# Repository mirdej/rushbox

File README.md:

# rushbox
controller for martin rush wash

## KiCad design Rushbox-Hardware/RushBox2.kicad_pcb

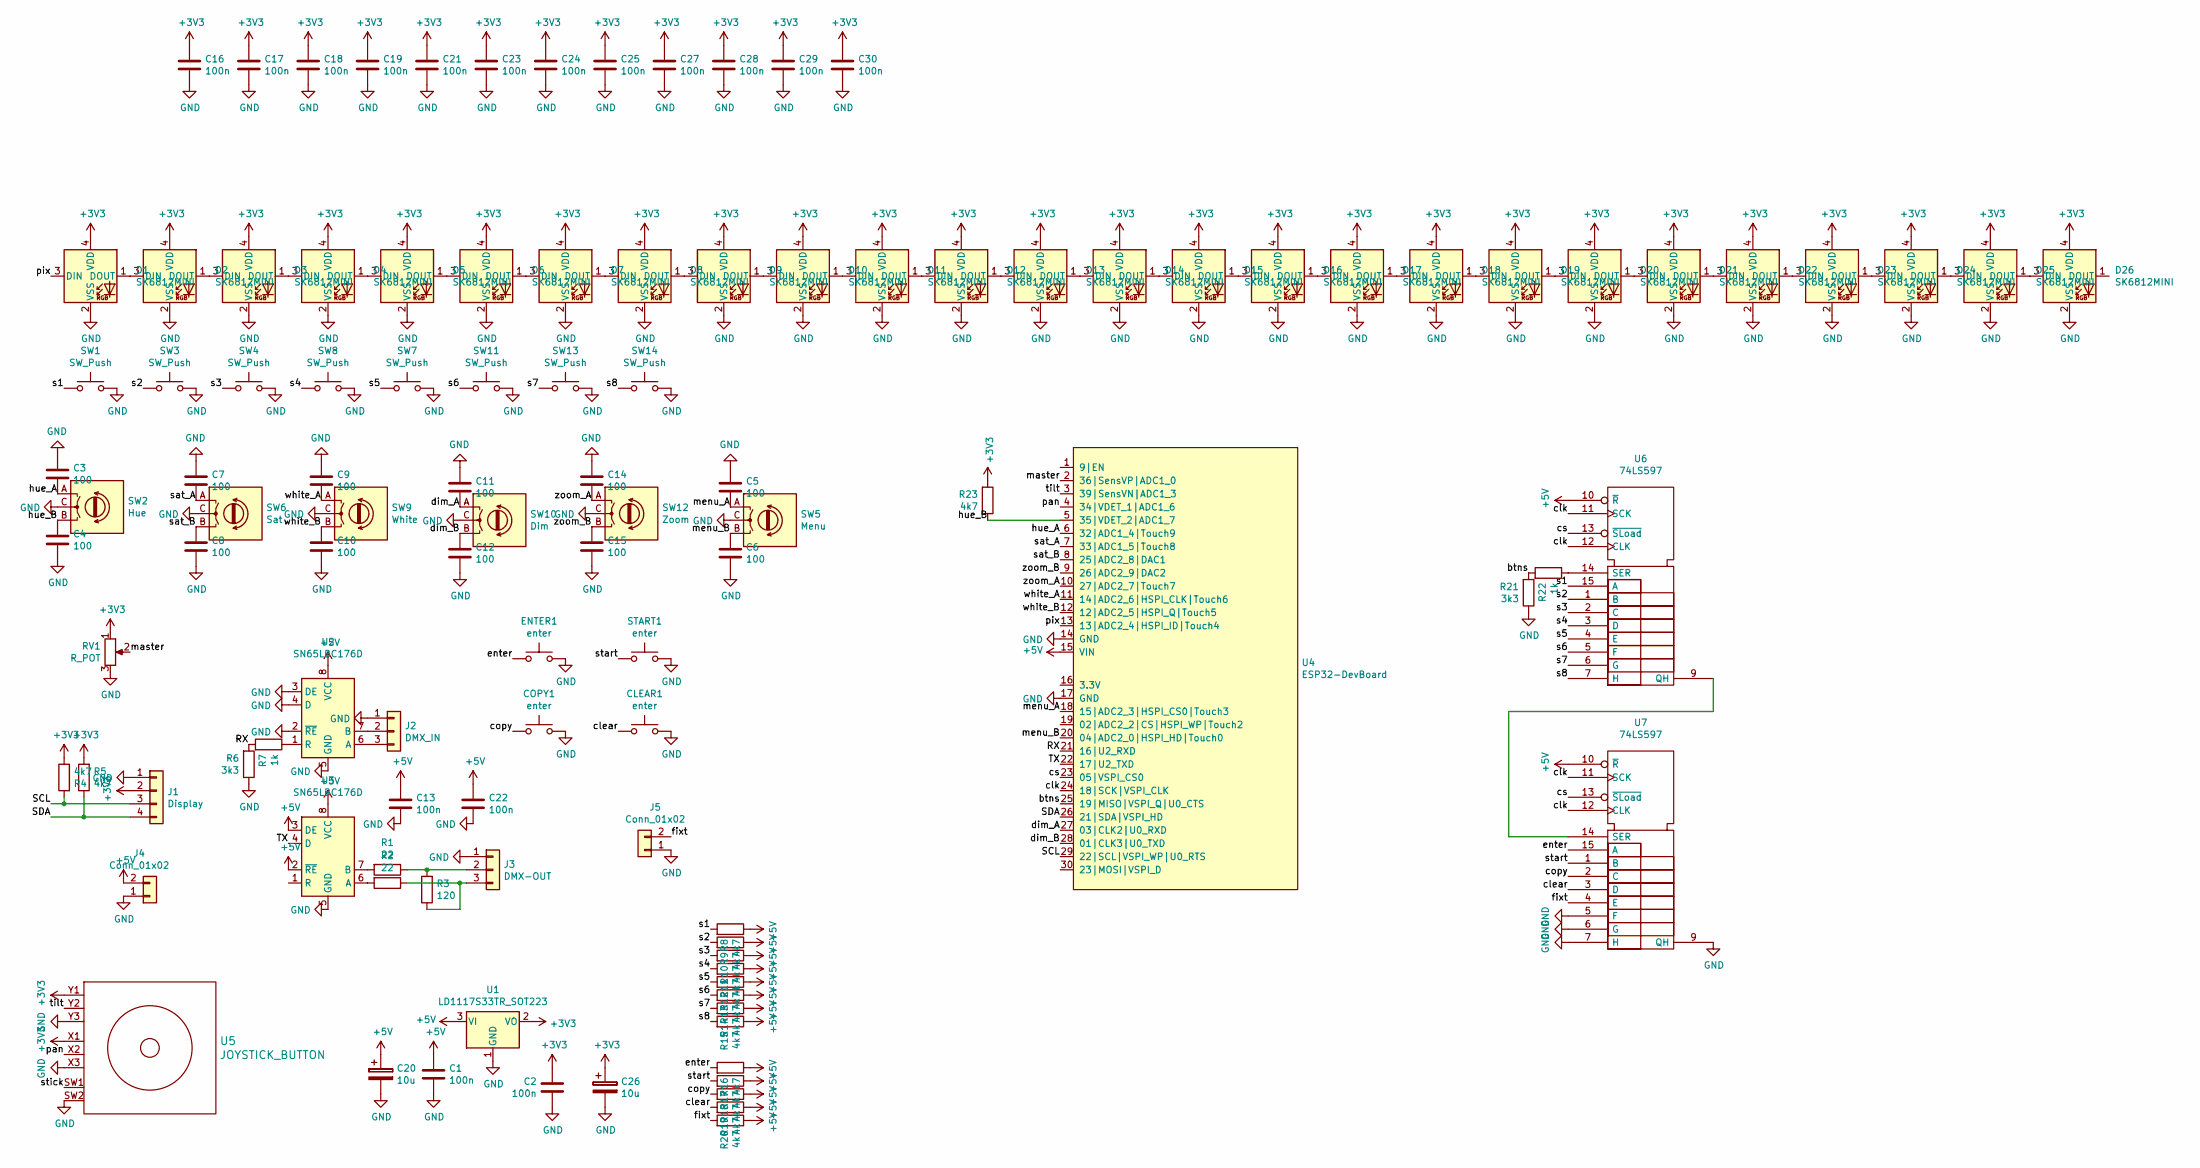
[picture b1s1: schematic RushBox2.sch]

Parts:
C1, C2, C13, C16, C17, C18, C19, C21, C22, C23, C24, C25, C27, C28, C29, C30: 100n; C_0603_1608Metric_Pad1.05x0.95mm_HandSolder
C3, C4, C5, C6, C7, C8, C9, C10, C11, C12, C14, C15: 100; C_0603_1608Metric_Pad1.05x0.95mm_HandSolder
C20, C26: 10u; CP_EIA-3528-21_Kemet-B_Pad1.50x2.35mm_HandSolder
CLEAR1: enter; SW_SPST_B3SL-1002P
COPY1: enter; SW_SPST_B3SL-1002P
D1, D2, D3, D4, D5, D6, D7, D8, D9, D10, D11, D12, D13, D14, D15, D16, D17, D18, D19, D20, D21, D22, D23, D24, D25, D26: SK6812MINI; LED_SK6812MINI_PLCC4_3.5x3.5mm_P1.75mm
ENTER1: enter; SW_SPST_B3SL-1002P
J1: Display; Bangood-OLED-128x32
J2: DMX_IN; Molex_KK-254_AE-6410-03A_1x03_P2.54mm_Vertical
J3: DMX-OUT; Molex_KK-254_AE-6410-03A_1x03_P2.54mm_Vertical
J4, J5: Conn_01x02; Molex_KK-254_AE-6410-02A_1x02_P2.54mm_Vertical
R1, R2: 22; R_0805_2012Metric_Pad1.15x1.40mm_HandSolder
R3: 120; R_0805_2012Metric_Pad1.15x1.40mm_HandSolder
R4, R5, R8, R9, R10, R11, R12, R13, R14, R15, R16, R17, R18, R19, R20, R23: 4k7; R_0805_2012Metric_Pad1.15x1.40mm_HandSolder
R6, R21: 3k3; R_0805_2012Metric_Pad1.15x1.40mm_HandSolder
R7, R22: 1k; R_0805_2012Metric_Pad1.15x1.40mm_HandSolder
RV1: R_POT; Potentiometer_Alps_RS6011xP_Slide
START1: enter; SW_SPST_B3SL-1002P
SW1, SW3, SW4, SW7, SW8, SW11, SW13, SW14: SW_Push; SW_SPST_B3SL-1002P
SW2: Hue; RotaryEncoder_Alps_EC12E_Vertical_H20mm
SW5: Menu; RotaryEncoder_Alps_EC12E_Vertical_H20mm
SW6: Sat; RotaryEncoder_Alps_EC12E_Vertical_H20mm
SW9: White; RotaryEncoder_Alps_EC12E_Vertical_H20mm
SW10: Dim; RotaryEncoder_Alps_EC12E_Vertical_H20mm
SW12: Zoom; RotaryEncoder_Alps_EC12E_Vertical_H20mm
U1: LD1117S33TR_SOT223; SOT-223-3_TabPin2
U2, U3: SN65LBC176D; SOIC-8_3.9x4.9mm_P1.27mm
U4: ESP32-DevBoard; ESP32_Devboard
U5: JOYSTICK_BUTTON; Joystick_Button
U6, U7: 74LS597; SOIC-16_3.9x9.9mm_P1.27mm

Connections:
+3V3: C2.2, C16.1, C17.1, C18.1, C19.1, C21.1, C23.1, C24.1, C25.1, C26.1, C27.1, C28.1, C29.1, C30.1, D1.4 (VDD), D2.4 (VDD), D3.4 (VDD), D4.4 (VDD), D5.4 (VDD), D6.4 (VDD), D7.4 (VDD), D8.4 (VDD), D9.4 (VDD), D10.4 (VDD), D11.4 (VDD), D12.4 (VDD), D13.4 (VDD), D14.4 (VDD), D15.4 (VDD), D16.4 (VDD), D17.4 (VDD), D18.4 (VDD), D19.4 (VDD), D20.4 (VDD), D21.4 (VDD), D22.4 (VDD), D23.4 (VDD), D24.4 (VDD), D25.4 (VDD), D26.4 (VDD), J1.2, R4.1, R5.2, R23.2, RV1.1, U1.2 (VO), U5.X1, U5.Y1
+5V: C1.1, C13.1, C20.1, C22.1, J4.2, R8.1, R9.1, R10.1, R11.1, R12.1, R13.1, R14.1, R15.1, R16.1, R17.1, R18.1, R19.1, R20.1, U1.3 (VI), U2.8 (VCC), U3.2 (~RE), U3.3 (DE), U3.8 (VCC), U4.15 (VIN), U6.10 (~R), U7.10 (~R)
/RX: R6.2, R7.2, U4.21 (16|U2_RXD)
/SCL: J1.3, R4.2, U4.29 (22|SCL|VSPI_WP|U0_RTS)
/SDA: J1.4, R5.1, U4.26 (21|SDA|VSPI_HD)
/TX: U3.4 (D), U4.22 (17|U2_TXD)
/btns: R21.2, R22.2, U4.25 (19|MISO|VSPI_Q|U0_CTS)
/clear: CLEAR1.1, R19.2, U7.3 (D)
/clk: U4.24 (18|SCK|VSPI_CLK), U6.11 (SCK), U6.12 (CLK), U7.11 (SCK), U7.12 (CLK)
/copy: COPY1.1, R18.2, U7.2 (C)
/cs: U4.23 (05|VSPI_CS0), U6.13 (~SLoad), U7.13 (~SLoad)
/dim_A: C11.2, SW10.A, U4.27 (03|CLK2|U0_RXD)
/dim_B: C12.1, SW10.B, U4.28 (01|CLK3|U0_TXD)
/enter: ENTER1.1, R16.2, U7.15 (A)
/fixt: J5.2, R20.2, U7.4 (E)
/hue_A: C3.2, SW2.A, U4.6 (32|ADC1_4|Touch9)
/hue_B: C4.1, R23.1, SW2.B, U4.5 (35|VDET_2|ADC1_7)
/master: RV1.2, U4.2 (36|SensVP|ADC1_0)
/menu_A: C5.2, SW5.A, U4.18 (15|ADC2_3|HSPI_CS0|Touch3)
/menu_B: C6.1, SW5.B, U4.20 (04|ADC2_0|HSPI_HD|Touch0)
/pan: U4.4 (34|VDET_1|ADC1_6), U5.X2
/pix: D1.3 (DIN), U4.13 (13|ADC2_4|HSPI_ID|Touch4)
/s1: R8.2, SW1.1, U6.15 (A)
/s2: R9.2, SW3.1, U6.1 (B)
/s3: R10.2, SW4.1, U6.2 (C)
/s4: R11.2, SW8.1, U6.3 (D)
/s5: R12.2, SW7.1, U6.4 (E)
/s6: R13.2, SW11.1, U6.5 (F)
/s7: R14.2, SW13.1, U6.6 (G)
/s8: R15.2, SW14.1, U6.7 (H)
/sat_A: C7.2, SW6.A, U4.7 (33|ADC1_5|Touch8)
/sat_B: C8.1, SW6.B, U4.8 (25|ADC2_8|DAC1)
/start: R17.2, START1.1, U7.1 (B)
/tilt: U4.3 (39|SensVN|ADC1_3), U5.Y2
/white_A: C9.2, SW9.A, U4.11 (14|ADC2_6|HSPI_CLK|Touch6)
/white_B: C10.1, SW9.B, U4.12 (12|ADC2_5|HSPI_Q|Touch5)
/zoom_A: C14.2, SW12.A, U4.10 (27|ADC2_7|Touch7)
/zoom_B: C15.1, SW12.B, U4.9 (26|ADC2_9|DAC2)
GND: C1.2, C2.1, C3.1, C4.2, C5.1, C6.2, C7.1, C8.2, C9.1, C10.2, C11.1, C12.2, C13.2, C14.1, C15.2, C16.2, C17.2, C18.2, C19.2, C20.2, C21.2, C22.2, C23.2, C24.2, C25.2, C26.2, C27.2, C28.2, C29.2, C30.2, CLEAR1.2, COPY1.2, D1.2 (VSS), D2.2 (VSS), D3.2 (VSS), D4.2 (VSS), D5.2 (VSS), D6.2 (VSS), D7.2 (VSS), D8.2 (VSS), D9.2 (VSS), D10.2 (VSS), D11.2 (VSS), D12.2 (VSS), D13.2 (VSS), D14.2 (VSS), D15.2 (VSS), D16.2 (VSS), D17.2 (VSS), D18.2 (VSS), D19.2 (VSS), D20.2 (VSS), D21.2 (VSS), D22.2 (VSS), D23.2 (VSS), D24.2 (VSS), D25.2 (VSS), D26.2 (VSS), ENTER1.2, J1.1, J2.1, J3.1, J4.1, J5.1, R6.1, R21.1, RV1.3, START1.2, SW1.2, SW2.C, SW3.2, SW4.2, SW5.C, SW6.C, SW7.2, SW8.2, SW9.C, SW10.C, SW11.2, SW12.C, SW13.2, SW14.2, U1.1 (GND), U2.2 (~RE), U2.3 (DE), U2.4 (D), U2.5 (GND), U3.5 (GND), U4.14 (GND), U4.17 (GND), U5.SW2, U5.X3, U5.Y3, U6.8 (GND), U7.5 (F), U7.6 (G), U7.7 (H), U7.8 (GND), U7.9 (QH)
unnamed: D1.1 (DOUT), D2.3 (DIN)
unnamed: D2.1 (DOUT), D3.3 (DIN)
unnamed: D3.1 (DOUT), D4.3 (DIN)
unnamed: D4.1 (DOUT), D5.3 (DIN)
unnamed: D5.1 (DOUT), D6.3 (DIN)
unnamed: D6.1 (DOUT), D7.3 (DIN)
unnamed: D7.1 (DOUT), D8.3 (DIN)
unnamed: D8.1 (DOUT), D9.3 (DIN)
unnamed: D10.1 (DOUT), D11.3 (DIN)
unnamed: D9.1 (DOUT), D10.3 (DIN)
unnamed: D11.1 (DOUT), D12.3 (DIN)
unnamed: D12.1 (DOUT), D13.3 (DIN)
unnamed: D13.1 (DOUT), D14.3 (DIN)
unnamed: D14.1 (DOUT), D15.3 (DIN)
unnamed: D15.1 (DOUT), D16.3 (DIN)
unnamed: D16.1 (DOUT), D17.3 (DIN)
unnamed: D17.1 (DOUT), D18.3 (DIN)
unnamed: D18.1 (DOUT), D19.3 (DIN)
unnamed: D19.1 (DOUT), D20.3 (DIN)
unnamed: D20.1 (DOUT), D21.3 (DIN)
unnamed: D21.1 (DOUT), D22.3 (DIN)
unnamed: D22.1 (DOUT), D23.3 (DIN)
unnamed: D23.1 (DOUT), D24.3 (DIN)
unnamed: D24.1 (DOUT), D25.3 (DIN)
unnamed: D25.1 (DOUT), D26.3 (DIN)
unnamed: J2.2, U2.7 (B)
unnamed: J2.3, U2.6 (A)
unnamed: J3.2, R1.1, R3.2
unnamed: J3.3, R2.1, R3.1
unnamed: R1.2, U3.7 (B)
unnamed: R2.2, U3.6 (A)
unnamed: R7.1, U2.1 (R)
unnamed: R22.1, U6.14 (SER)
unnamed: U6.9 (QH), U7.14 (SER)
VCC: U6.16 (VCC), U7.16 (VCC)

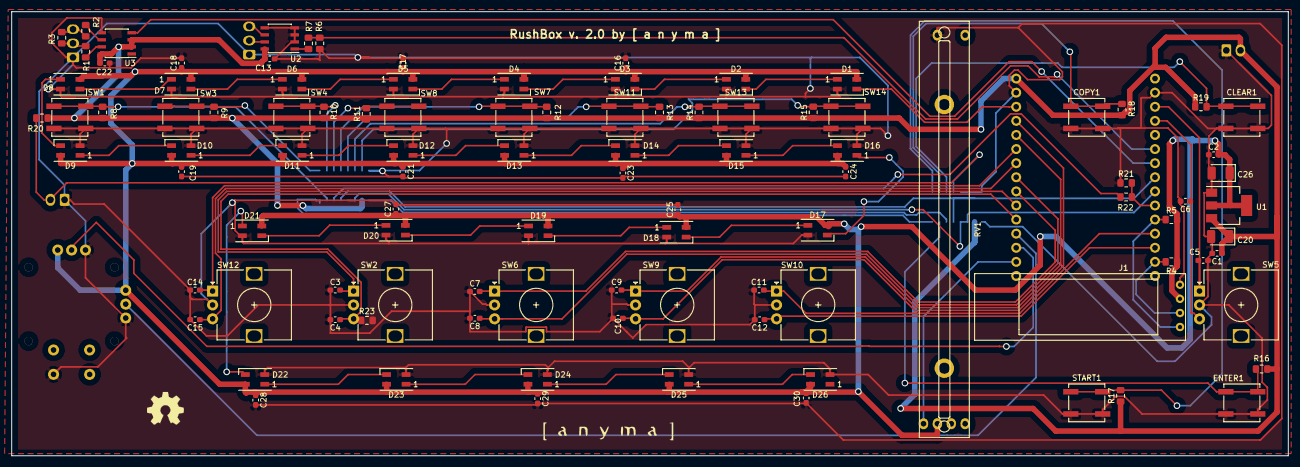
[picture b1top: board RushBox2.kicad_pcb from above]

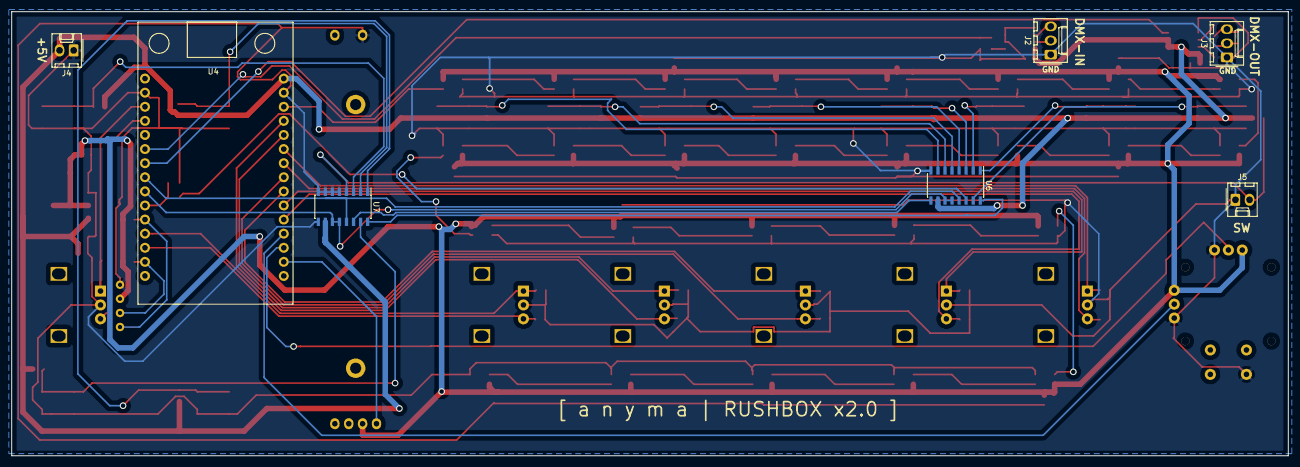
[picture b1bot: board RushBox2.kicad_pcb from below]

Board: 2 copper layers, 230.0 x 80.0 mm, 110 parts (7 on the bottom side), 74 nets.

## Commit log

2019-11-26 add hardware
2019-11-26 pin 35 is input only. add pullup resistor. did not reroute board
2019-11-26 pin 2 not good for encoder because of builtin led
2019-11-27 74HC597 missing supply, works on 3v3 as well, change pull up rail to 3v3, wrong connections on 74hc597 inversed serial output and input. update schematic to reflect corrections. bord not routed
2019-11-27 add fetus firmware and enclosure model
2019-11-28 add RushWash class
2019-11-29 can set fixture addresses from browser
2019-12-02 basic fixture control. lee filters, copying, resetting
2019-12-02 can save and recall scenes. copy and delete
2019-12-02 change bank
2019-12-03 add colorspace and bootstrap-toggle
